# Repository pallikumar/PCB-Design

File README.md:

# PCB-Design
Breadboard Power Supply PCB Design using KiCad
**Overview**
This repository contains the files for a breadboard power supply PCB design created using KiCad version 7. The project aims to provide a step-by-step guide on designing a PCB from scratch using KiCad, from schematic capture to manufacturing.

**Files Included**
Schematic: The schematic diagram (.sch) file outlines the circuit components and connections.
PCB Layout: The PCB layout (.kicad_pcb) file represents the physical layout of components on the PCB.
Gerber Files: Gerber files (.gbr) are included for manufacturing the PCB.
Bill of Materials (BOM): A BOM (.csv) listing all components used in the design.
3D Models: 3D models (.step) of components for visualization.

**Design Process**
**1. Schematic Design**
Launch KiCad and create a new project.
Draw the schematic diagram by adding components from the KiCad library.
Connect components using wires to represent electrical connections.
Label nets and add necessary annotations.
Check for errors and annotate the schematic.
Save the schematic.

**2. PCB Layout**
Open the PCB layout editor in KiCad.
Import the netlist generated from the schematic.
Place components on the PCB layout, considering factors like component orientation, size, and signal routing.
Route traces to connect components, ensuring proper clearance and avoiding signal interference.
Add necessary design elements like mounting holes, silkscreen labels, and copper pours.
Perform design rule checks (DRC) to ensure the design meets manufacturing requirements.
Generate Gerber files for manufacturing.

**3. Manufacturing**
Upload Gerber files to a PCB manufacturer's website.
Specify manufacturing options such as board material, thickness, and surface finish.
Review design files and confirm the order.
Wait for the manufacturer to produce and deliver the PCBs.

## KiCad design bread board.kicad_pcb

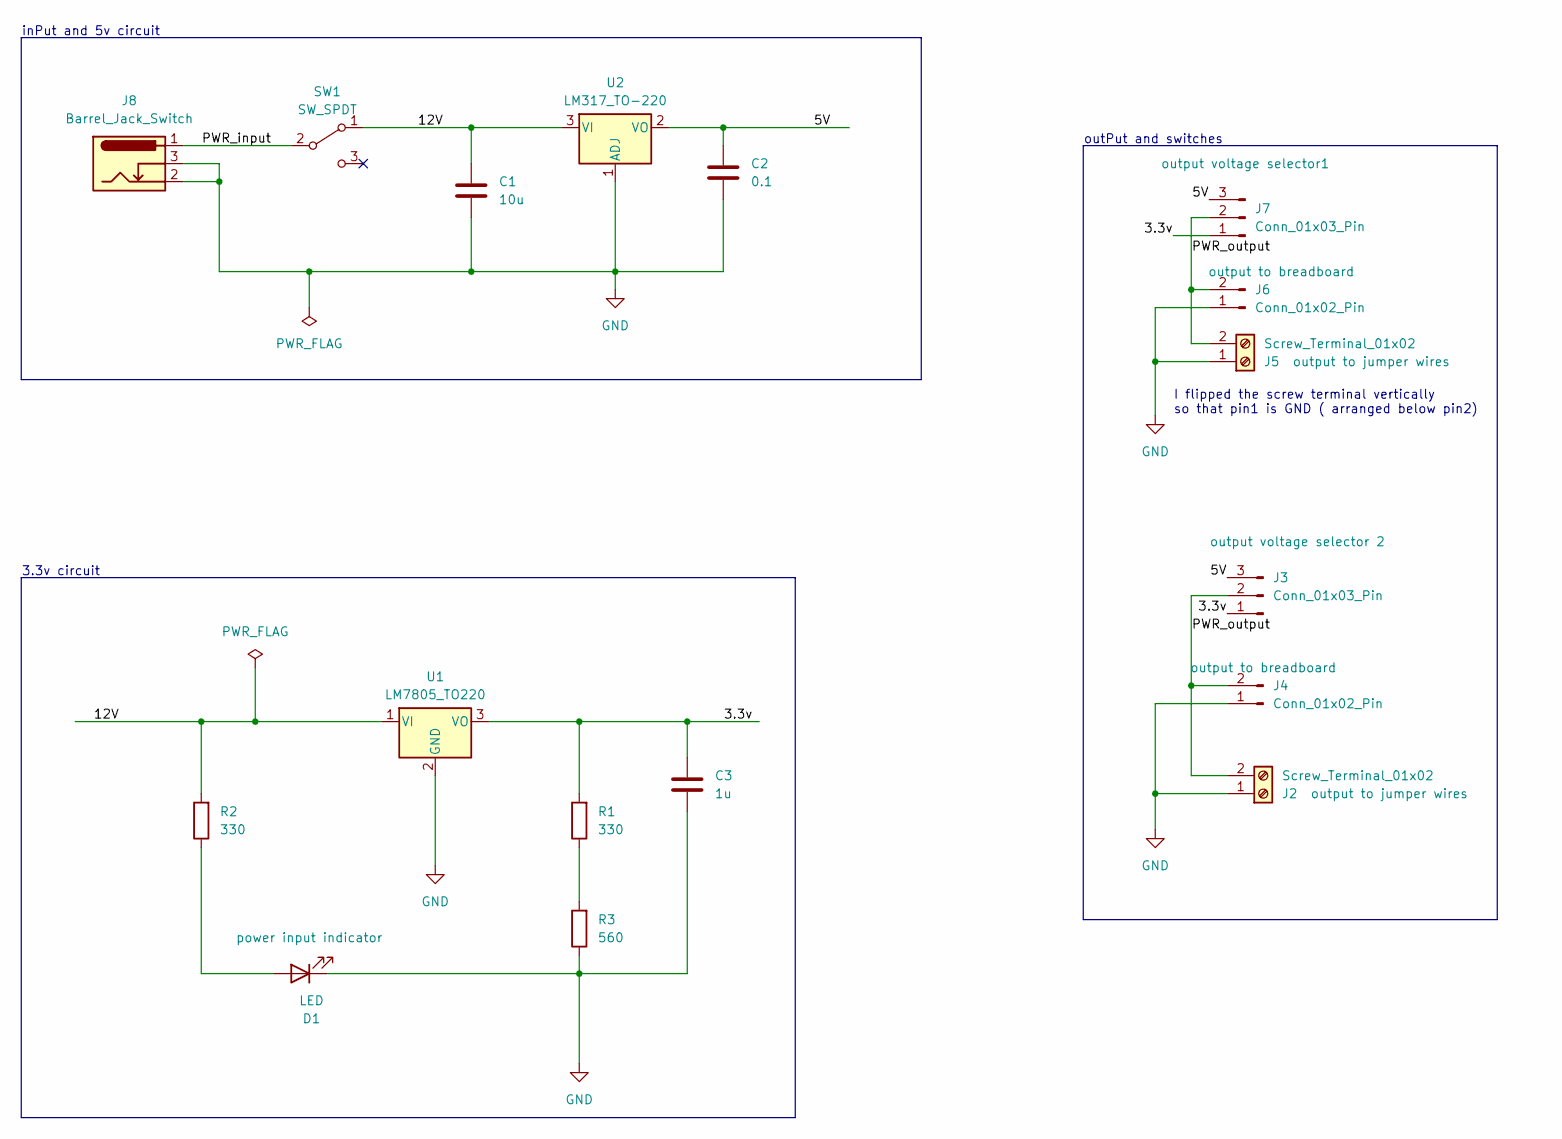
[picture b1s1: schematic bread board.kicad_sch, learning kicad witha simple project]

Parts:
C1: 10u; C_Disc_D3.0mm_W1.6mm_P2.50mm
C2: 0.1; C_Disc_D3.0mm_W1.6mm_P2.50mm
C3: 1u; C_Disc_D3.0mm_W1.6mm_P2.50mm
D1: LED; LED_D5.0mm
J2, J5: Screw_Terminal_01x02; TerminalBlock_bornier-2_P5.08mm
J3, J7: Conn_01x03_Pin; PinHeader_1x03_P2.54mm_Vertical
J4, J6: Conn_01x02_Pin; PinHeader_1x02_P2.54mm_Vertical
J8: Barrel_Jack_Switch; BarrelJack_Horizontal
R1, R2: 330; R_Axial_DIN0204_L3.6mm_D1.6mm_P7.62mm_Horizontal
R3: 560; R_Axial_DIN0204_L3.6mm_D1.6mm_P7.62mm_Horizontal
SW1: SW_SPDT; SW_DIP_SPSTx01_Slide_6.7x4.1mm_W8.61mm_P2.54mm_LowProfile
U1: LM7805_TO220; TO-220-3_Vertical
U2: LM317_TO-220; TO-220-3_Vertical

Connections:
/3.3v: C3.1, J3.1, J7.1, R1.2, U1.3 (VO)
/5V: C2.1, J3.3, J7.3, U2.2 (VO)
/12V: C1.1, R2.2, SW1.1 (A), U1.1 (VI), U2.3 (VI)
/PWR_input: J8.1, SW1.2 (B)
/PWR_output: J2.2, J3.2, J4.2, J5.2, J6.2, J7.2
GND: C1.2, C2.2, C3.2, D1.1 (K), J2.1, J4.1, J5.1, J6.1, J8.2, J8.3, R3.1, U1.2 (GND), U2.1 (ADJ)
unnamed: D1.2 (A), R2.1
unnamed: R1.1, R3.2

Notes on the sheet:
inPut and 5v circuit
outPut and switches
3.3v circuit
I flipped the screw terminal vertically so that pin1 is GND ( arranged below pin2)

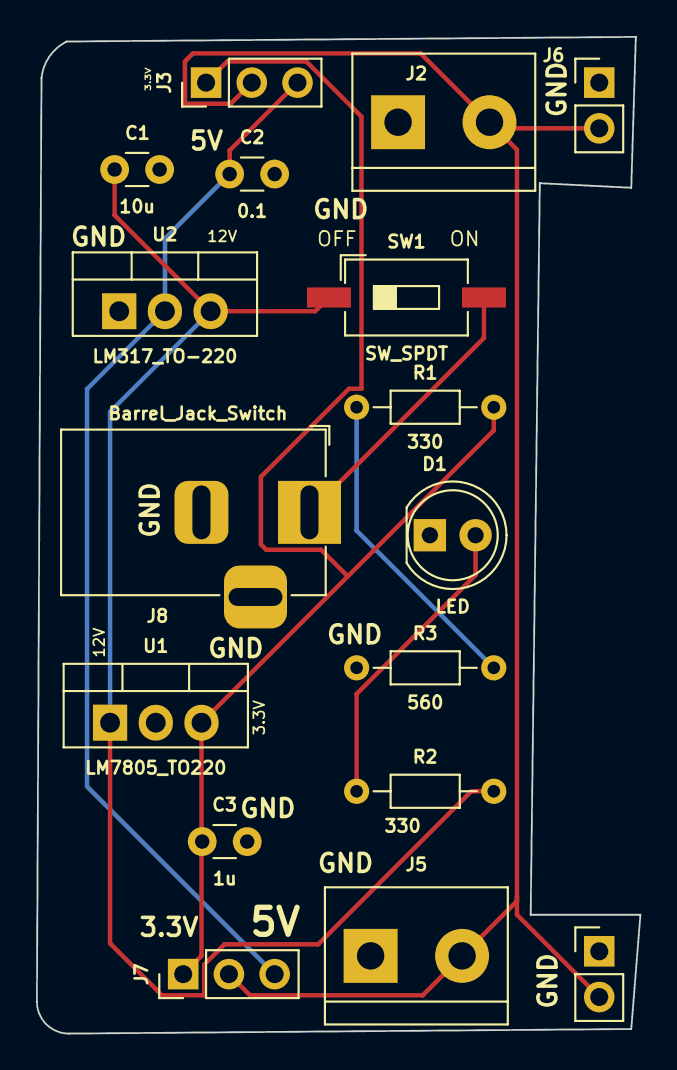
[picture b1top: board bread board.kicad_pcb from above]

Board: 2 copper layers, 33.5 x 55.4 mm, 17 parts (0 on the bottom side), 8 nets.
